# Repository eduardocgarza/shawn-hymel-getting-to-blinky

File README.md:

# PCB Project 1 - Getting to Blinky

**Tutorial Series:**

[YouTube KiCad Tutorial - Shawn Hymel - PCB Design](https://www.youtube.com/playlist?list=PL3bNyZYHcRSUhUXUt51W6nKvxx2ORvUQB)

## Outcome

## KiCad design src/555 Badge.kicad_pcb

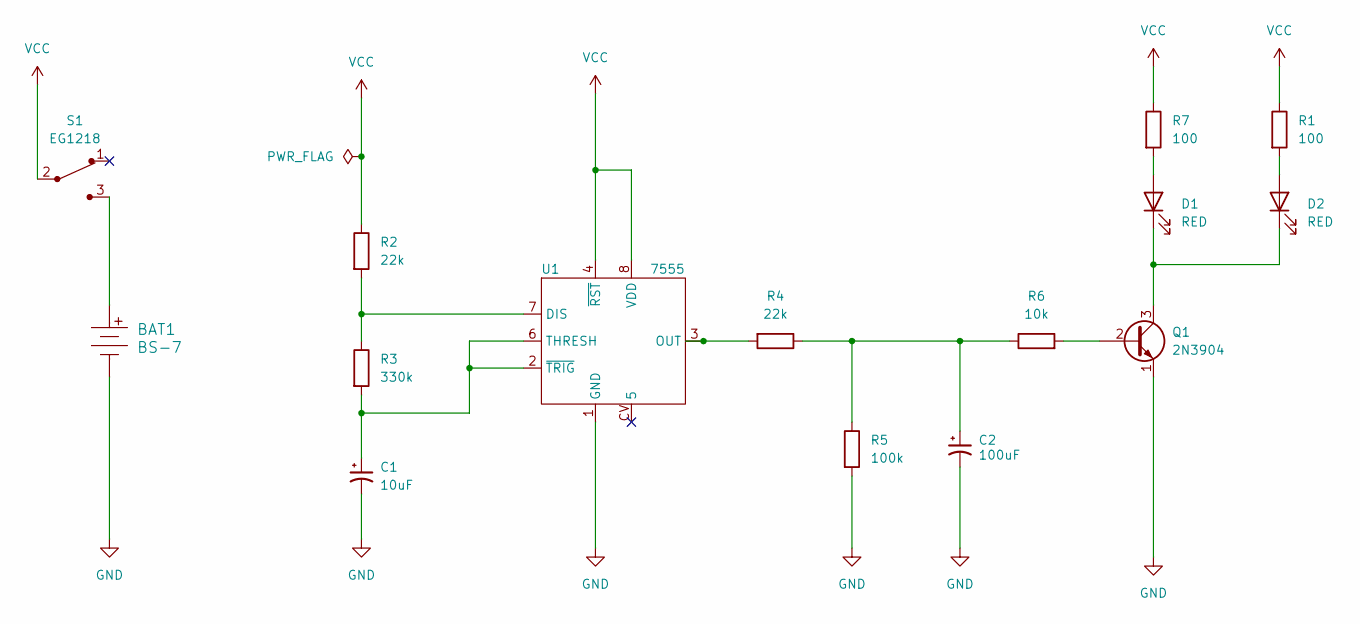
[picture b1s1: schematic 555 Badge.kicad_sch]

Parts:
BAT1: BS-7; Battery_Holder_Coin_2032_BS-7; MPN BS-7; Digi-Key_PN BS-7-ND
C1: 10uF; CP_Radial_D5.0mm_P2.00mm
C2: 100uF; CP_Radial_D5.0mm_P2.50mm
D1, D2: RED; LED_D3.0mm
Q1: 2N3904; TO-92-3
R1, R7: 100; R_Axial_DIN0207_L6.3mm_D2.5mm_P7.62mm_Horizontal
R2, R4: 22k; R_Axial_DIN0207_L6.3mm_D2.5mm_P7.62mm_Horizontal
R3: 330k; R_Axial_DIN0207_L6.3mm_D2.5mm_P7.62mm_Horizontal
R5: 100k; R_Axial_DIN0207_L6.3mm_D2.5mm_P7.62mm_Horizontal
R6: 10k; R_Axial_DIN0207_L6.3mm_D2.5mm_P7.62mm_Horizontal
S1: EG1218; Switch_Slide_11.6x4mm_EG1218; MPN EG1218; Digi-Key_PN EG1903-ND
U1: 7555; ICM7555IPAZ-PDIP

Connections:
GND: BAT1.Neg, C1.2, C2.2, Q1.1 (E), R5.2, U1.1 (GND)
unnamed: BAT1.Pos, S1.3
unnamed: C2.1, R4.1, R5.1, R6.1
unnamed: D1.2 (A), R7.2
unnamed: D1.1 (K), D2.1 (K), Q1.3 (C)
unnamed: D2.2 (A), R1.2
unnamed: Q1.2 (B), R6.2
unnamed: R2.2, R3.1, U1.7 (DIS)
unnamed: R4.2, U1.3 (OUT)
unnamed: C1.1, R3.2, U1.2 (~TRIG), U1.6 (THRESH)
VCC: R1.1, R2.1, R7.1, S1.2, U1.4 (~RST), U1.8 (VDD)

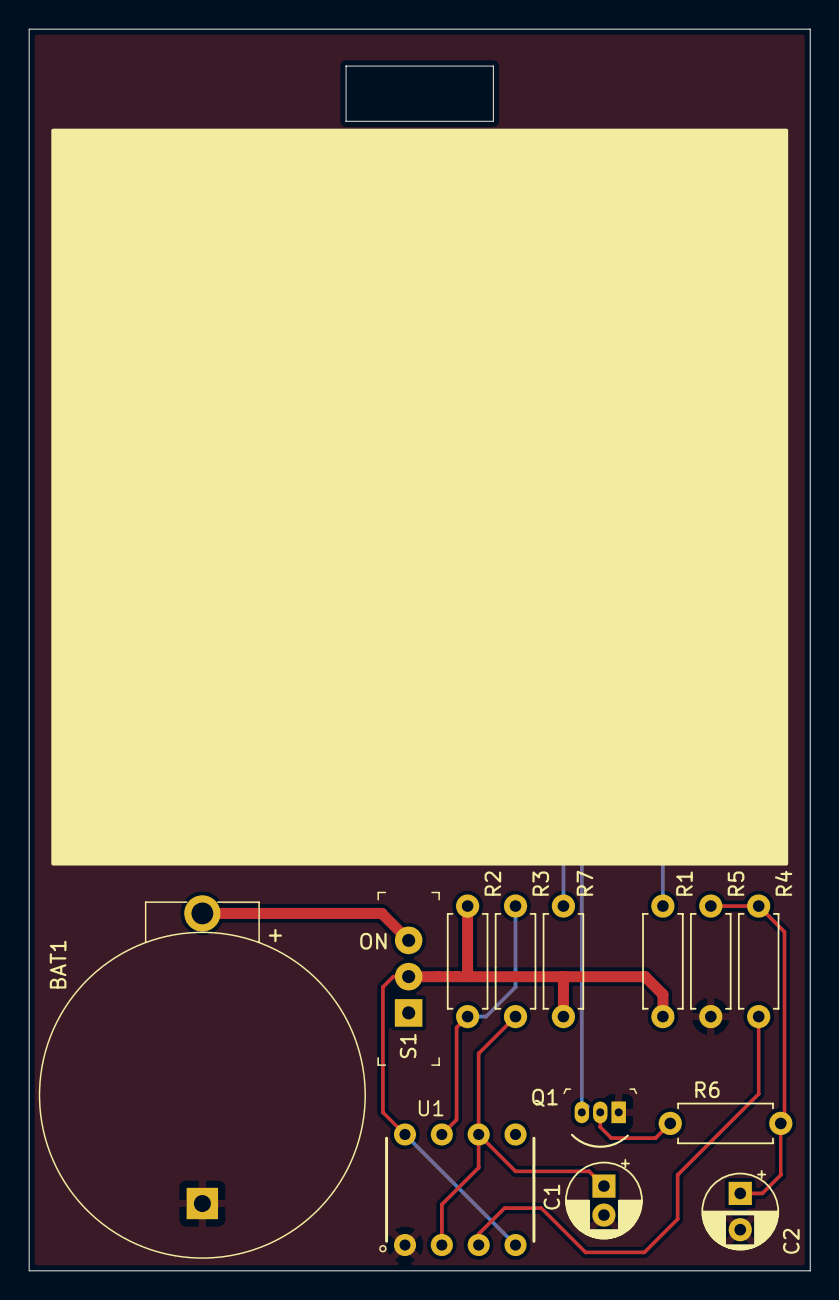
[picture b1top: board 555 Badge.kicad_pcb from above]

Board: 2 copper layers, 53.8 x 85.6 mm, 15 parts (0 on the bottom side), 11 nets.

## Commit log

2024-06-28 Adding project from local
2024-06-28 Added assets
2024-06-28 Removed venv and added project

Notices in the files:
src/555 Badge.kicad_pcb:
License: CC by 4.0
